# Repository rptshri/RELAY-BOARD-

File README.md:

# RELAY-BOARD-
RELAY BOARD SCHEMATICS AND LAYOUT
#CAN BE CUT FROM MIDDLE.

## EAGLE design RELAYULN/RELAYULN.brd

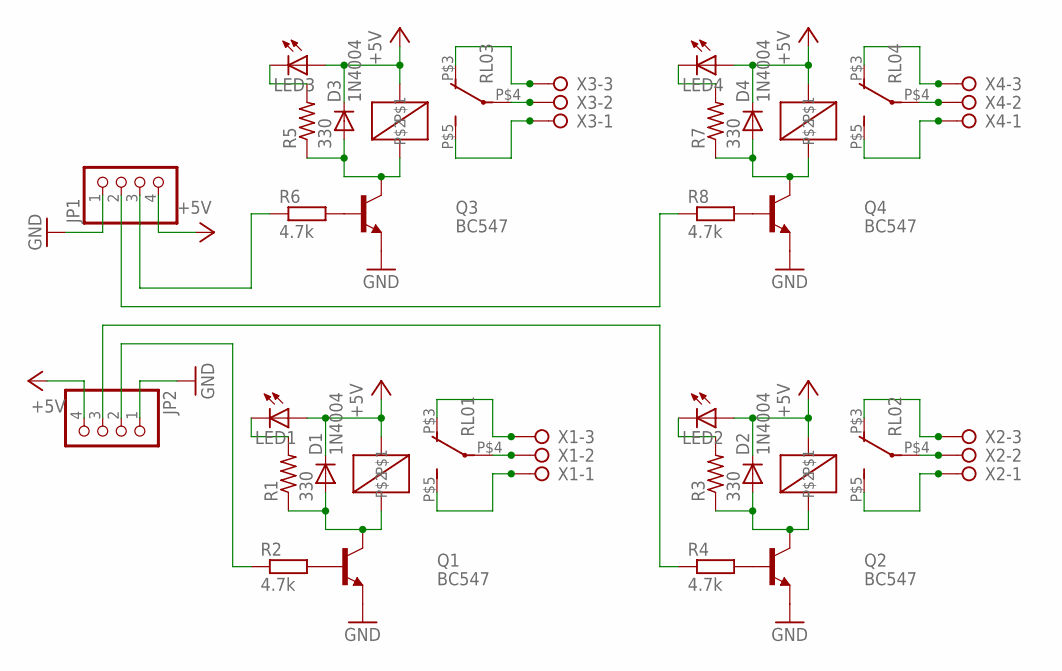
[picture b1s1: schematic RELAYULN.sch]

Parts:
D1, D2, D3, D4: 1N4004; DO41-10
JP1, JP2: PINHD-1X4; 1X04
LED1, LED2, LED3, LED4: LED3MM
Q1, Q2, Q3, Q4: BC547; TO92
R1, R3, R5, R7: 330; 0207/7
R2, R4, R6, R8: 4.7k; 0207/7
RL01, RL02, RL03, RL04: RELAY01
X1, X2, X3, X4: W237-3E

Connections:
+5V: D1.C, D2.C, D3.C, D4.C, JP1.4, JP2.4, LED1.A, LED2.A, LED3.A, LED4.A, RL01.P$2, RL02.P$2, RL03.P$2, RL04.P$2
GND: JP1.1, JP2.1, Q1.1 (E), Q2.1 (E), Q3.1 (E), Q4.1 (E)
unnamed: RL02.P$3 (O), X2.3
unnamed: RL02.P$4, X2.2
unnamed: RL02.P$5 (S), X2.1
unnamed: RL01.P$3 (O), X1.3
unnamed: RL01.P$4, X1.2
unnamed: RL01.P$5 (S), X1.1
unnamed: LED1.K (C), R1.2
unnamed: LED2.K (C), R3.2
unnamed: D1.A, Q1.3 (C), R1.1, RL01.P$1
unnamed: Q1.2 (B), R2.2
unnamed: D2.A, Q2.3 (C), R3.1, RL02.P$1
unnamed: Q2.2 (B), R4.2
unnamed: JP2.3, R4.1
unnamed: RL03.P$3 (O), X3.3
unnamed: RL03.P$4, X3.2
unnamed: RL03.P$5 (S), X3.1
unnamed: LED3.K (C), R5.2
unnamed: D3.A, Q3.3 (C), R5.1, RL03.P$1
unnamed: Q3.2 (B), R6.2
unnamed: JP1.3, R6.1
unnamed: RL04.P$3 (O), X4.3
unnamed: RL04.P$4, X4.2
unnamed: RL04.P$5 (S), X4.1
unnamed: LED4.K (C), R7.2
unnamed: D4.A, Q4.3 (C), R7.1, RL04.P$1
unnamed: Q4.2 (B), R8.2
unnamed: JP1.2, R8.1
unnamed: JP2.2, R2.1

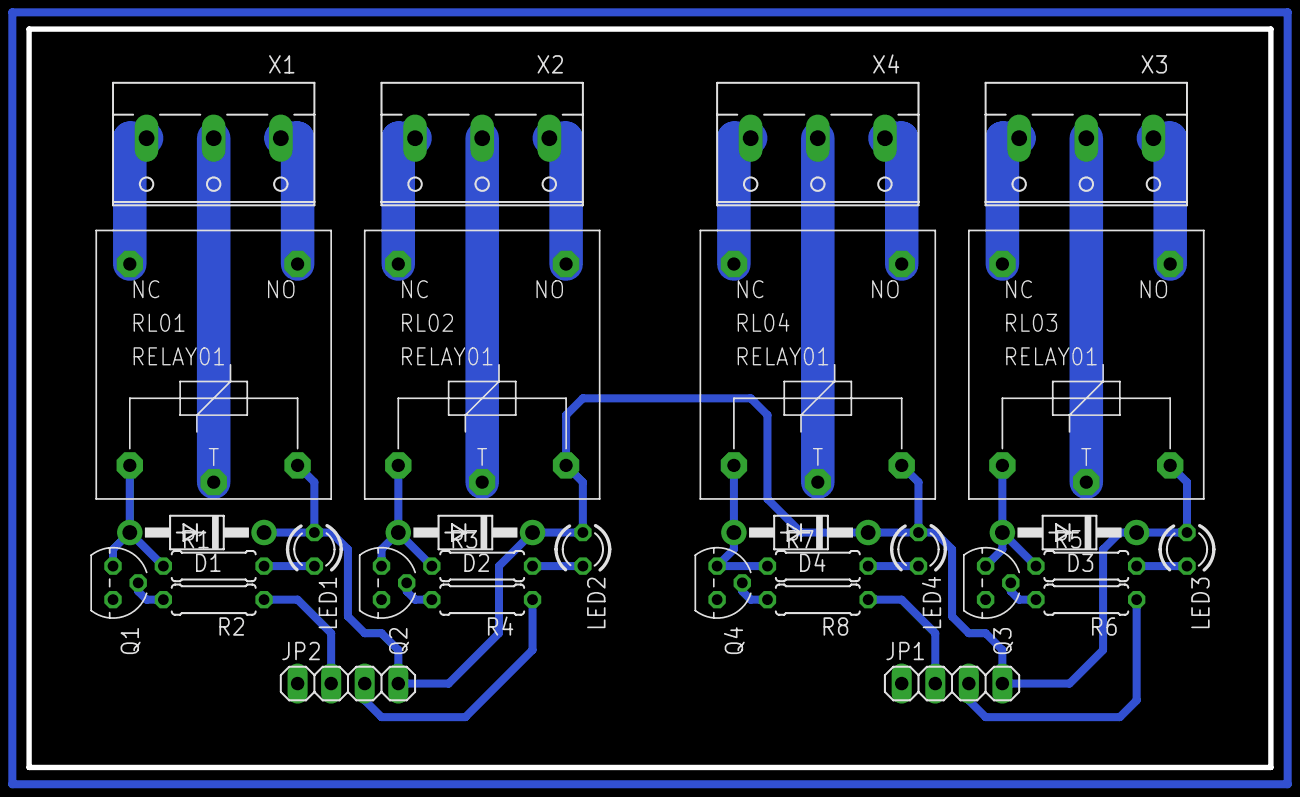
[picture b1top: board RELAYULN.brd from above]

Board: 2 copper layers, 94.0 x 55.9 mm, 30 parts (0 on the bottom side), 30 nets.
